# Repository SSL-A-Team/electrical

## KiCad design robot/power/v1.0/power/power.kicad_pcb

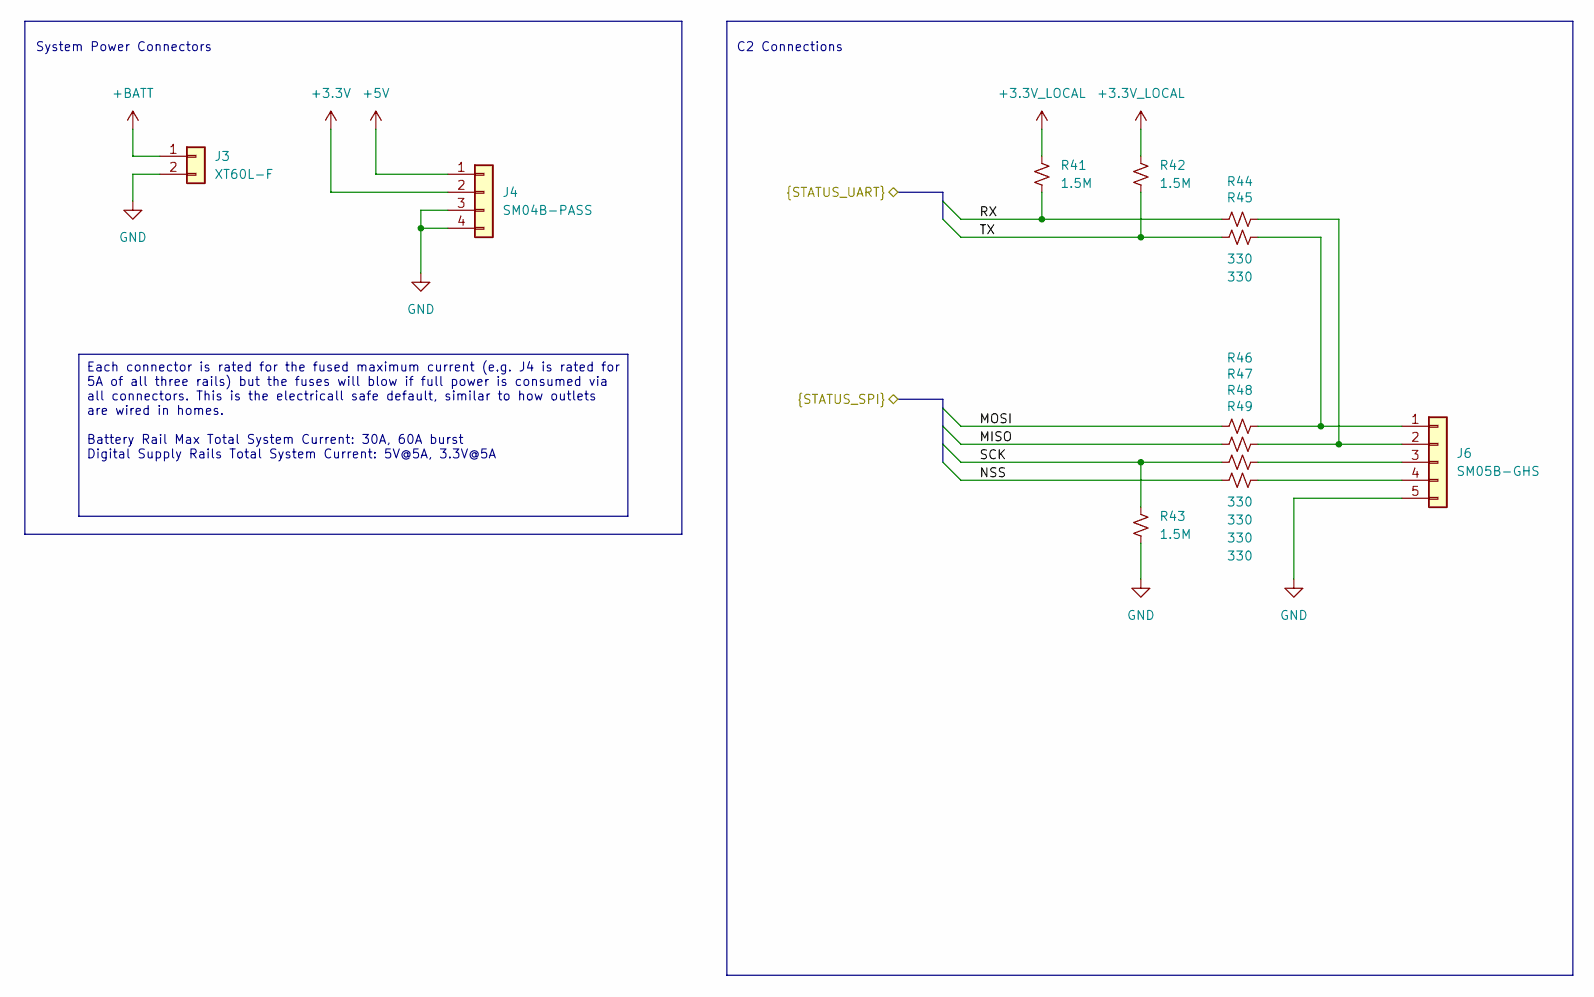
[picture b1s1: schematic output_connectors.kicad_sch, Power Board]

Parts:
J3: XT60L-F; AMASS_XT60PW-F_1x02_P7.20mm_Horizontal
J4: SM04B-PASS; JST_PA_S04B-PASS_1x04_P2.00mm_Horizontal
J6: SM05B-GHS; JST_GH_SM05B-GHS-TB_1x05-1MP_P1.25mm_Horizontal
R41, R42, R43: 1.5M; R_0402_1005Metric
R44, R45, R46, R47, R48, R49: 330; R_0402_1005Metric

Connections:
+3.3V: J4.2; also elsewhere on the board
+3.3V_LOCAL: R41.1, R42.1; also elsewhere on the board
+5V: J4.1; also elsewhere on the board
+BATT: J3.1; also elsewhere on the board
/mcu/MISO: R47.1; also elsewhere on the board
/mcu/MOSI: R46.1; also elsewhere on the board
/mcu/NSS: R49.1; also elsewhere on the board
/mcu/RX: R41.2, R44.1; also elsewhere on the board
/mcu/SCK: R43.1, R48.1; also elsewhere on the board
/mcu/TX: R42.2, R45.1; also elsewhere on the board
GND: J3.2, J4.3, J4.4, J6.5, R43.2; also elsewhere on the board
unnamed: J6.1, R45.2, R46.2
unnamed: J6.2, R44.2, R47.2
unnamed: J6.3, R48.2
unnamed: J6.4, R49.2

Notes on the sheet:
Each connector is rated for the fused maximum current (e.g. J4 is rated for 5A of all three rails) but the fuses will blow if full power is consumed via all connectors. This is the electricall safe default, similar to how outlets are wired in homes. Battery Rail Max Total System Current: 30A, 60A b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
C2 Connections
System Power Connectors

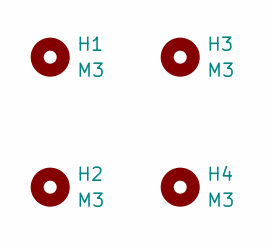
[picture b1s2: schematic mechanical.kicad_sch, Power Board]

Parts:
H1, H2, H3, H4: M3; MountingHole_3.2mm_M3_Pad_TopBottom

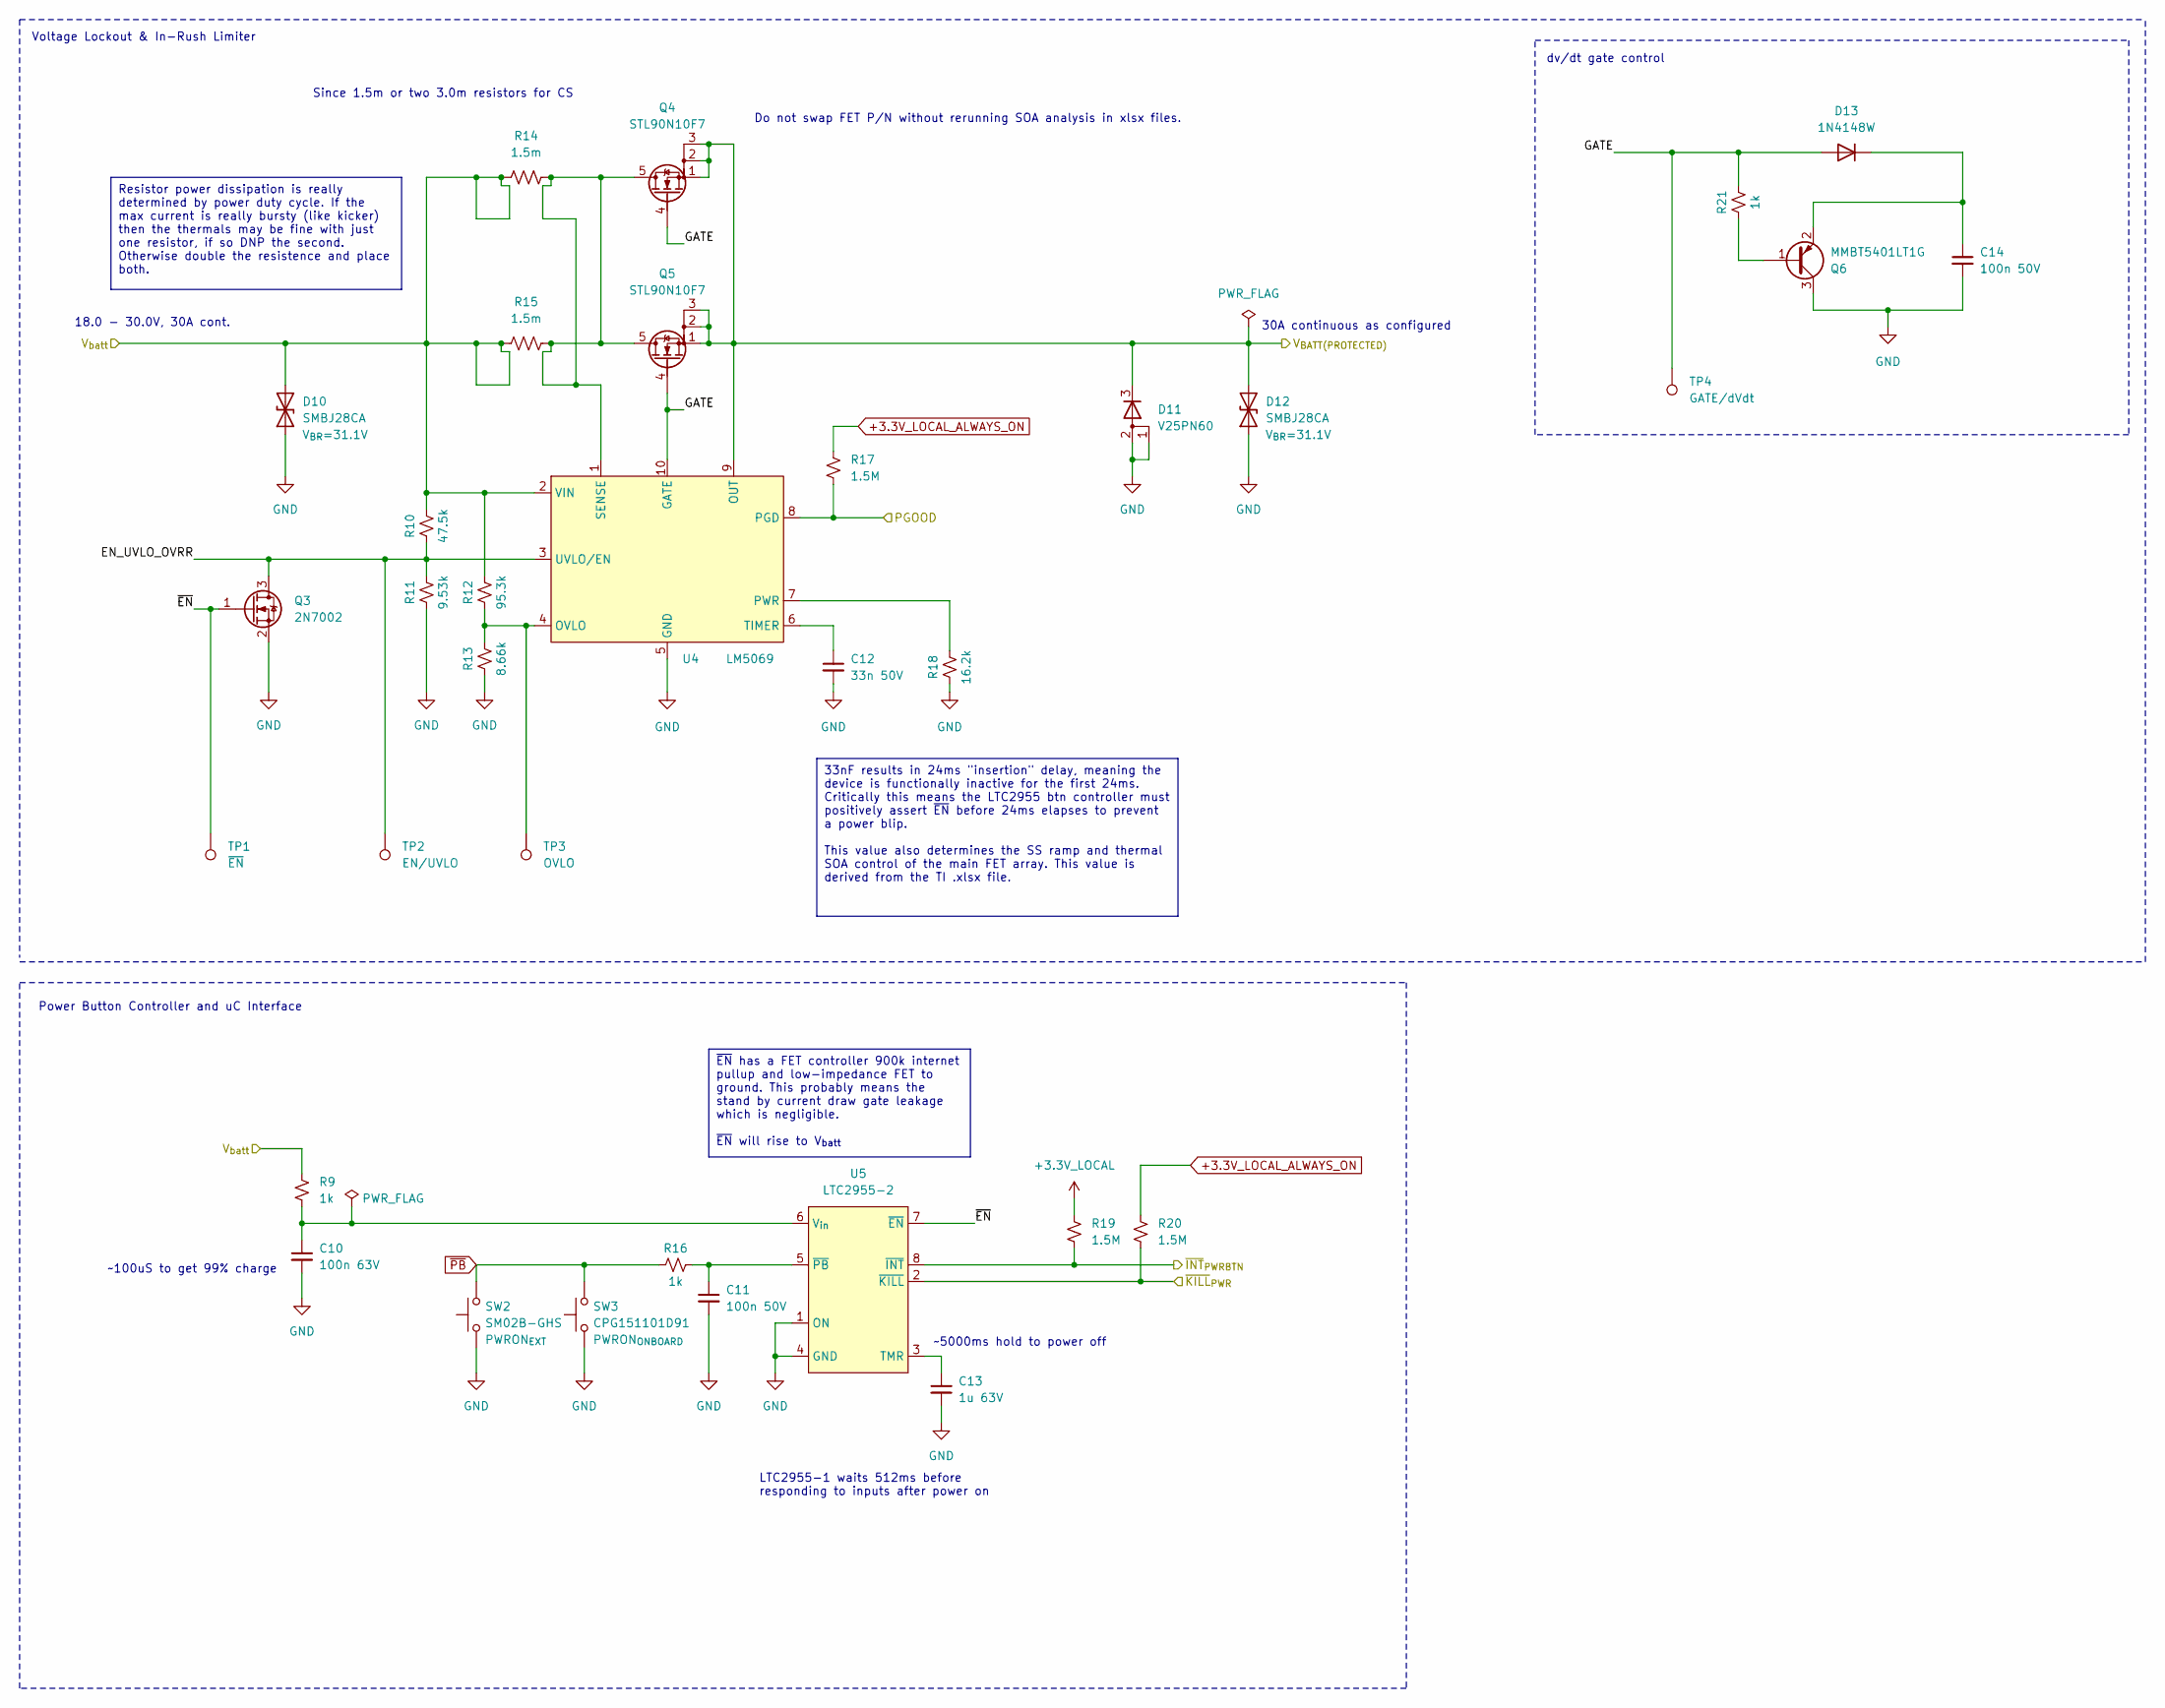
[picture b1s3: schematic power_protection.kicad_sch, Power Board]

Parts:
C10: 100n 63V; C_0402_1005Metric
C11, C14: 100n 50V; C_0402_1005Metric
C12: 33n 50V; C_0402_1005Metric
C13: 1u 63V; C_1206_3216Metric
D10, D12: SMBJ28CA; D_SMB_Non-Polar
D11: V25PN60; TO-277A
D13: 1N4148W; D_SOD-123
Q3: 2N7002; SOT-23
Q4, Q5: STL90N10F7; PowerFLAT_5x6
Q6: MMBT5401LT1G; SOT-23
R9, R16, R21: 1k; R_0402_1005Metric
R10: 47.5k; R_0402_1005Metric
R11: 9.53k; R_0402_1005Metric
R12: 95.3k; R_0402_1005Metric
R13: 8.66k; R_0402_1005Metric
R14, R15: 1.5m; R_2512_6332Metric
R17, R19, R20: 1.5M; R_0402_1005Metric
R18: 16.2k; R_0402_1005Metric
SW2: SM02B-GHS; JST_GH_SM02B-GHS-TB_1x02-1MP_P1.25mm_Horizontal
SW3: CPG151101D91; SW_SPST_TL3305A
TP1: ~{EN}; TestPoint_Pad_D2.5mm
TP2: EN/UVLO; TestPoint_Pad_D2.5mm
TP3: OVLO; TestPoint_Pad_D2.5mm
TP4: GATE/dVdt; TestPoint_Pad_D2.5mm
U4: LM5069; VSSOP-10_3x3mm_P0.5mm
U5: LTC2955-2; TSOT-23-8_HandSoldering

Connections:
+3.3V_LOCAL: R19.1; also elsewhere on the board
+3.3V_LOCAL_ALWAYS_ON: R17.1, R20.1; also elsewhere on the board
+BATT: D11.3 (K), D12.2 (A2), Q4.1 (S), Q4.2 (S), Q4.3 (S), Q5.1 (S), Q5.2 (S), Q5.3 (S), U4.9 (OUT); also elsewhere on the board
+V_{batt_fused}: D10.2 (A2), R9.2, R10.1, R12.1, R14.1, R15.1, U4.2 (VIN); also elsewhere on the board
/mcu/LOAD_SW_PGOOD: R17.2, U4.8 (PGD); also elsewhere on the board
/mcu/PWR_BTN_~INT: R19.2, U5.8 (~INT); also elsewhere on the board
/mcu/PWR_~KILL: R20.2, U5.2 (~KILL); also elsewhere on the board
/power_protection/EN_UVLO_OVRR: Q3.3 (D), R10.2, R11.1, TP2.1, U4.3 (UVLO/EN)
/power_protection/GATE: D13.2 (A), Q4.4 (G), Q5.4 (G), R21.1, TP4.1, U4.10 (GATE)
/power_protection/~EN: Q3.1 (G), TP1.1, U5.7 (~EN)
GND: C10.2, C11.2, C12.2, C13.2, C14.2, D10.1 (A1), D11.1 (A), D11.2 (A), D12.1 (A1), Q3.2 (S), Q6.3 (C), R11.2, R13.2, R18.2, SW2.1, SW3.1, U4.5 (GND), U5.1 (ON), U5.4 (GND); also elsewhere on the board
unnamed: C14.1, D13.1 (K), Q6.2 (E)
unnamed: Q4.5 (D), Q5.5 (D), R14.2, R15.2, U4.1 (SENSE)
unnamed: Q6.1 (B), R21.2
unnamed: R12.2, R13.1, TP3.1, U4.4 (OVLO)
unnamed: R18.1, U4.7 (PWR)
unnamed: C12.1, U4.6 (TIMER)
unnamed: C13.1, U5.3 (TMR)
unnamed: C10.1, R9.1, U5.6 (V_{in})
unnamed: C11.1, R16.1, U5.5 (~PB)
~PB: R16.2, SW2.2, SW3.2; also elsewhere on the board

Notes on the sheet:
~{EN} has a FET controller 900k internet pullup and low-impedance FET to ground. This probably means the stand by current draw gate leakage which is negligible. ~{EN} will rise to V_{batt}
Resistor power dissipation is really determined by power duty cycle. If the max current is really bursty (like kicker) then the thermals may be fine with just one resistor, if so DNP the second. Otherwise double the resistence and place both.
33nF results in 24ms "insertion" delay, meaning the device is functionally inactive for the first 24ms. Critically this means the LTC2955 btn controller must positively assert ~{EN} before 24ms elapses to prevent a power blip. This value also determines the SS ramp and thermal SOA control of the ma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
18.0 - 30.0V, 30A cont.
30A continuous as configured
Voltage Lockout & In-Rush Limiter
Since 1.5m or two 3.0m resistors for CS
~5000ms hold to power off
dv/dt gate control
LTC2955-1 waits 512ms before responding to inputs after power on
Power Button Controller and uC Interface
Do not swap FET P/N without rerunning SOA analysis in xlsx files.
~100uS to get 99% charge

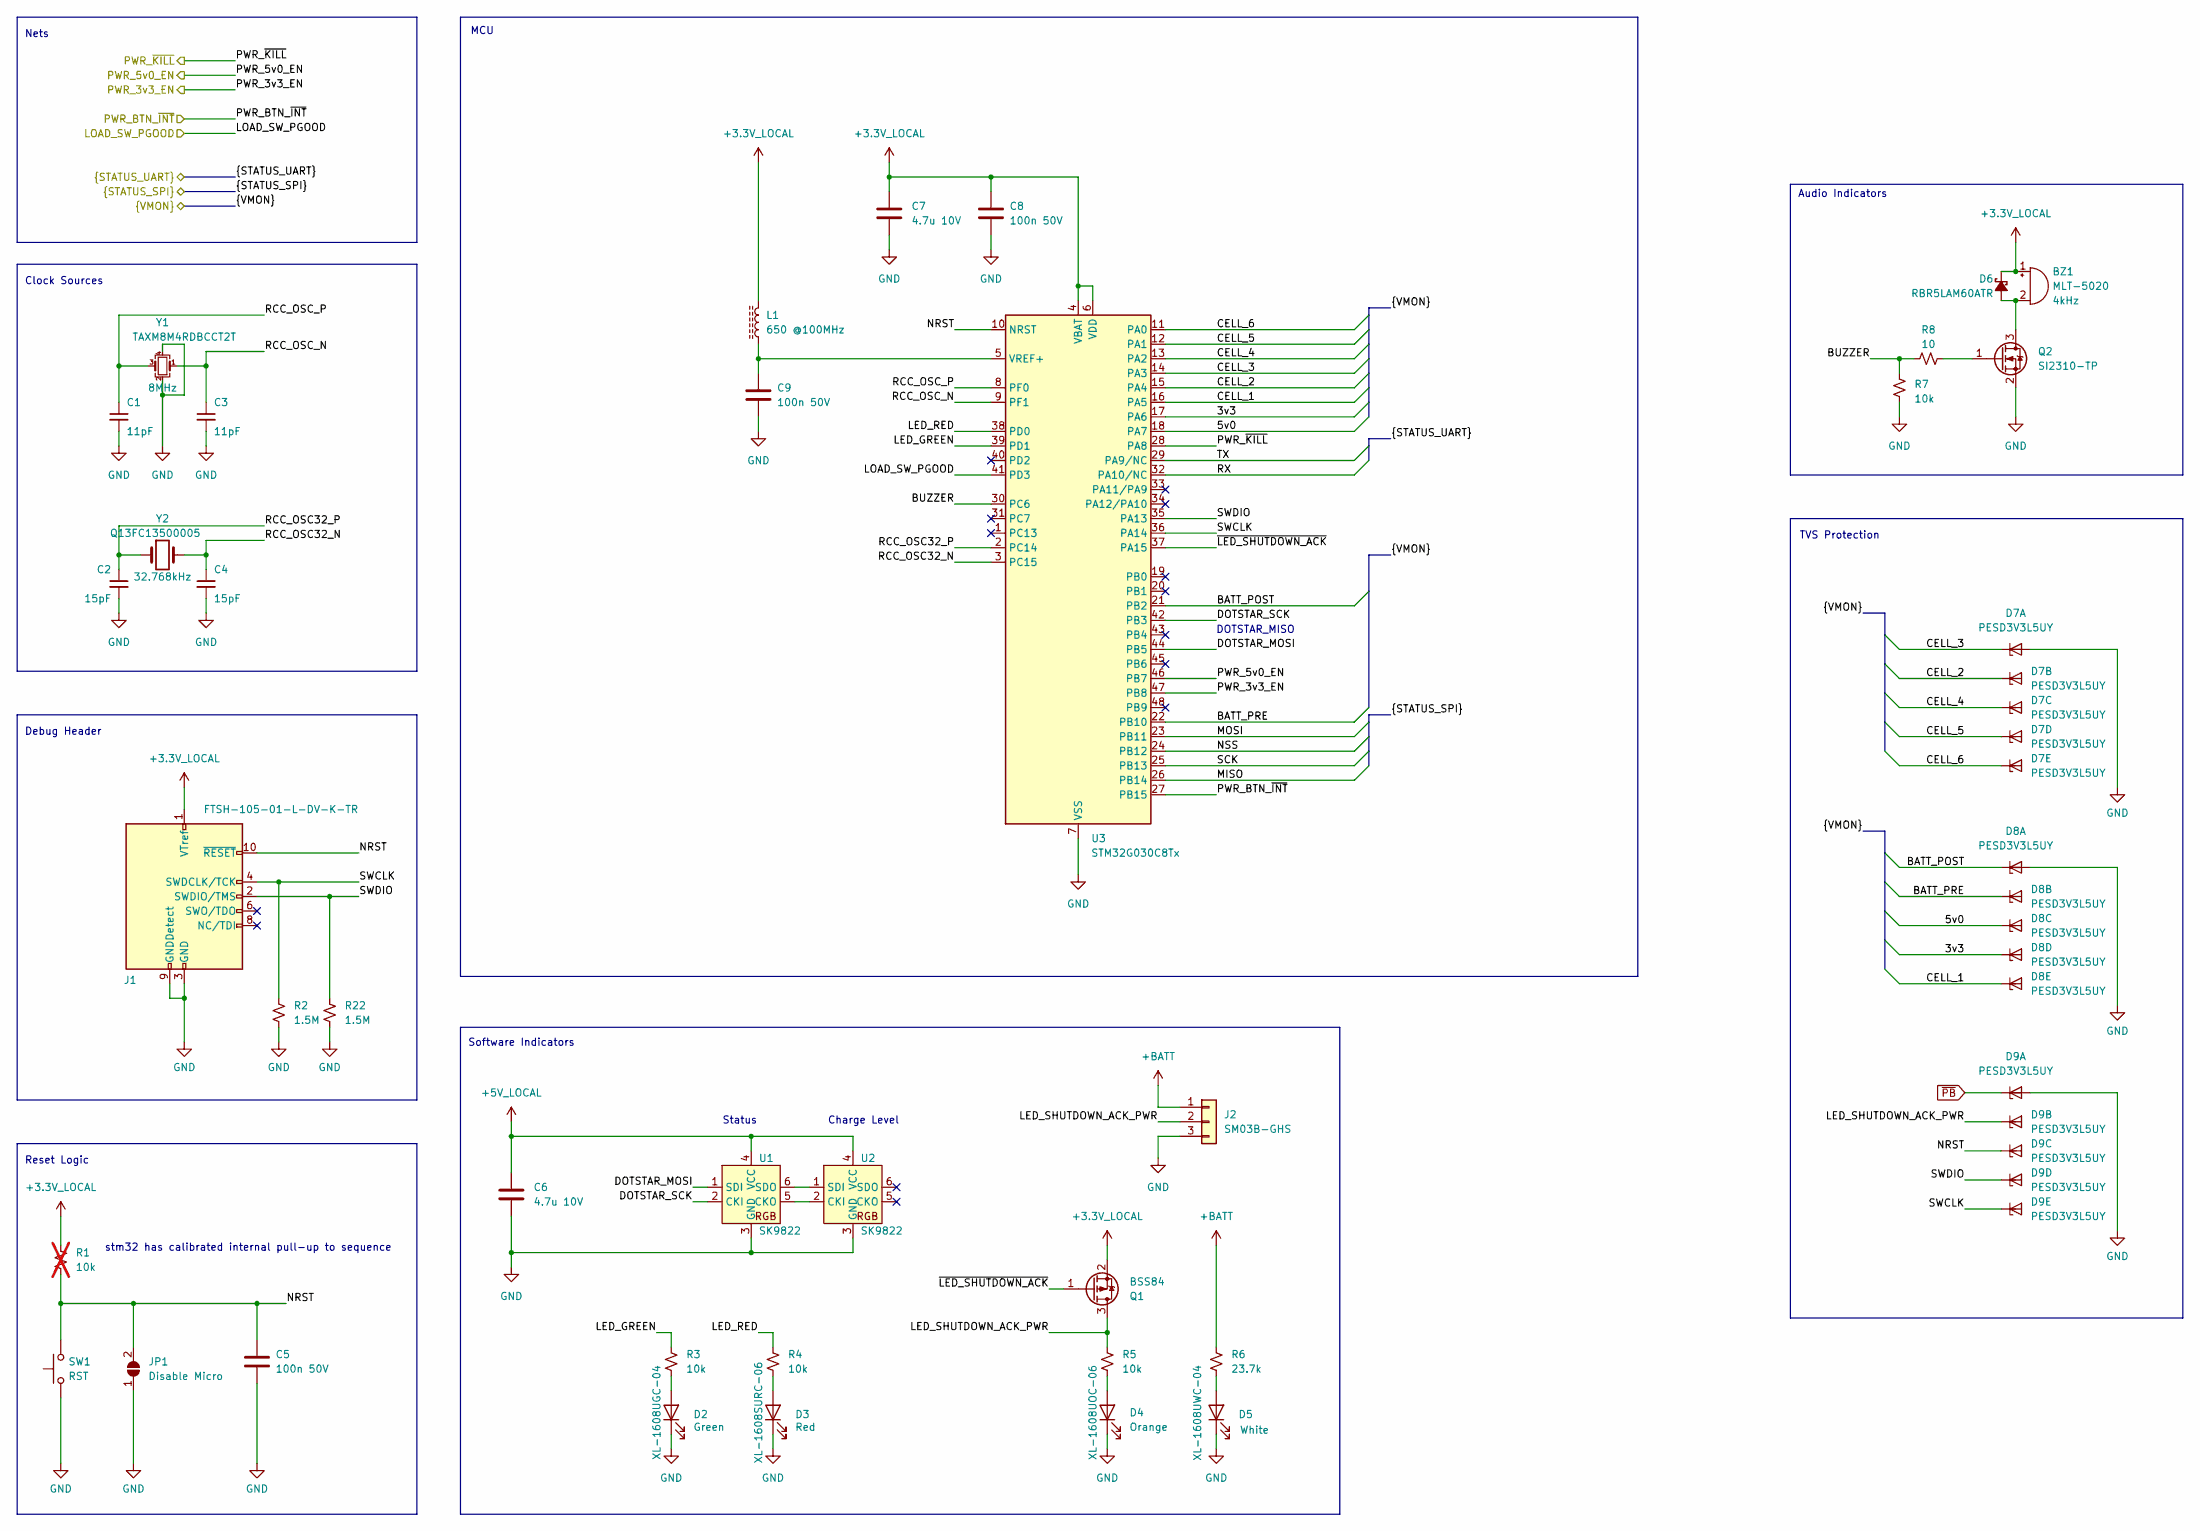
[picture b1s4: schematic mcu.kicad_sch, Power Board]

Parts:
BZ1: MLT-5020
C1, C3: 11pF; C_0402_1005Metric
C2, C4: 15pF; C_0402_1005Metric
C5, C8, C9: 100n 50V; C_0402_1005Metric
C6, C7: 4.7u 10V; C_0402_1005Metric
D2: XL-1608UGC-04; LED0603
D3: XL-1608SURC-06; LED0603
D4: XL-1608UOC-06; LED0603
D5: XL-1608UWC-04; LED0603
D6: RBR5LAM60ATR; D_SOD-128
D7, D8, D9: PESD3V3L5UY; SOT-363_SC-70-6
J1: FTSH-105-01-L-DV-K-TR; Samtec-2x5pin-0.5mm
J2: SM03B-GHS; JST_GH_SM03B-GHS-TB_1x03-1MP_P1.25mm_Horizontal
JP1: Disable Micro; SolderJumper-2_2.0x1.2mm_Open
L1: 650 @100MHz; R_0603_1608Metric
Q1: BSS84; SOT-23
Q2: SI2310-TP; SOT-23
R1: 10k; R_0402_1005Metric; not fitted
R2, R22: 1.5M; R_0402_1005Metric
R3, R4, R5, R7: 10k; R_0402_1005Metric
R6: 23.7k; R_0402_1005Metric
R8: 10; R_0402_1005Metric
SW1: RST; SW_SPST_TL3305A
U1, U2: SK9822
U3: STM32G030C8Tx; LQFP-48_7x7mm_P0.5mm
Y1: TAXM8M4RDBCCT2T; Crystal_SMD_3225-4Pin_3.2x2.5mm
Y2: Q13FC13500005; Crystal_SMD_3215-2Pin_3.2x1.5mm

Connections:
+3.3V_LOCAL: BZ1.1 (-), C7.1, C8.1, D6.1 (K), J1.1 (VTref), L1.2, Q1.2 (S), R1.1, U3.4 (VBAT), U3.6 (VDD); also elsewhere on the board
+5V_LOCAL: C6.2, U1.4 (VCC), U2.4 (VCC); also elsewhere on the board
+BATT: J2.1, R6.1; also elsewhere on the board
/mcu/3v3: D8.5 (K4), U3.17 (PA6); also elsewhere on the board
/mcu/5v0: D8.4 (K3), U3.18 (PA7); also elsewhere on the board
/mcu/BATT_POST: D8.1 (K1), U3.21 (PB2); also elsewhere on the board
/mcu/BATT_PRE: D8.3 (K2), U3.22 (PB10); also elsewhere on the board
/mcu/BUZZER: R7.1, R8.1, U3.30 (PC6)
/mcu/CELL_1: D8.6 (K5), U3.16 (PA5); also elsewhere on the board
/mcu/CELL_2: D7.3 (K2), U3.15 (PA4); also elsewhere on the board
/mcu/CELL_3: D7.1 (K1), U3.14 (PA3); also elsewhere on the board
/mcu/CELL_4: D7.4 (K3), U3.13 (PA2); also elsewhere on the board
/mcu/CELL_5: D7.5 (K4), U3.12 (PA1); also elsewhere on the board
/mcu/CELL_6: D7.6 (K5), U3.11 (PA0); also elsewhere on the board
/mcu/DOTSTAR_MOSI: U1.1 (SDI), U3.44 (PB5)
/mcu/DOTSTAR_SCK: U1.2 (CKI), U3.42 (PB3)
/mcu/LED_GREEN: R3.1, U3.39 (PD1)
/mcu/LED_RED: R4.1, U3.38 (PD0)
/mcu/LED_SHUTDOWN_ACK_PWR: D9.3 (K2), J2.2, Q1.3 (D), R5.1
/mcu/LOAD_SW_PGOOD: U3.41 (PD3); also elsewhere on the board
/mcu/MISO: U3.26 (PB14); also elsewhere on the board
/mcu/MOSI: U3.23 (PB11); also elsewhere on the board
/mcu/NRST: C5.1, D9.4 (K3), J1.10 (~RESET), JP1.2 (B), R1.2, SW1.2, U3.10 (NRST)
/mcu/NSS: U3.24 (PB12); also elsewhere on the board
/mcu/PWR_3v3_EN: U3.47 (PB8); also elsewhere on the board
/mcu/PWR_5v0_EN: U3.46 (PB7); also elsewhere on the board
/mcu/PWR_BTN_~INT: U3.27 (PB15); also elsewhere on the board
/mcu/PWR_~KILL: U3.28 (PA8); also elsewhere on the board
/mcu/RCC_OSC32_N: C4.1, U3.3 (PC15), Y2.2
/mcu/RCC_OSC32_P: C2.1, U3.2 (PC14), Y2.1
/mcu/RCC_OSC_N: C3.1, U3.9 (PF1), Y1.1
/mcu/RCC_OSC_P: C1.1, U3.8 (PF0), Y1.3
/mcu/RX: U3.32 (PA10/NC); also elsewhere on the board
/mcu/SCK: U3.25 (PB13); also elsewhere on the board
/mcu/SWCLK: D9.6 (K5), J1.4 (SWDCLK/TCK), R2.1, U3.36 (PA14)
/mcu/SWDIO: D9.5 (K4), J1.2 (SWDIO/TMS), R22.1, U3.35 (PA13)
/mcu/TX: U3.29 (PA9/NC); also elsewhere on the board
/mcu/~LED_SHUTDOWN_ACK: Q1.1 (G), U3.37 (PA15)
GND: C1.2, C2.2, C3.2, C4.2, C5.2, C6.1, C7.2, C8.2, C9.2, D2.1 (K), D3.1 (K), D4.1 (K), D5.1 (K), D7.2 (A), D8.2 (A), D9.2 (A), J1.3 (GND), J1.5 (GND), J1.9 (GNDDetect), J2.3, JP1.1 (A), Q2.2 (S), R2.2, R7.2, R22.2, SW1.1, U1.3 (GND), U2.3 (GND), U3.7 (VSS), Y1.2, Y1.4; also elsewhere on the board
unnamed: BZ1.2 (+), D6.2 (A), Q2.3 (D)
unnamed: D2.2 (A), R3.2
unnamed: D3.2 (A), R4.2
unnamed: D4.2 (A), R5.2
unnamed: D5.2 (A), R6.2
unnamed: Q2.1 (G), R8.2
unnamed: U1.5 (CKO), U2.2 (CKI)
unnamed: U1.6 (SDO), U2.1 (SDI)
unnamed: C9.1, L1.1, U3.5 (VREF+)
~PB: D9.1 (K1); also elsewhere on the board

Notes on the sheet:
Charge Level
Nets
Reset Logic
Audio Indicators
stm32 has calibrated internal pull-up to sequence
Clock Sources
TVS Protection
Status
Software Indicators
MCU
Debug Header
DOTSTAR_MISO

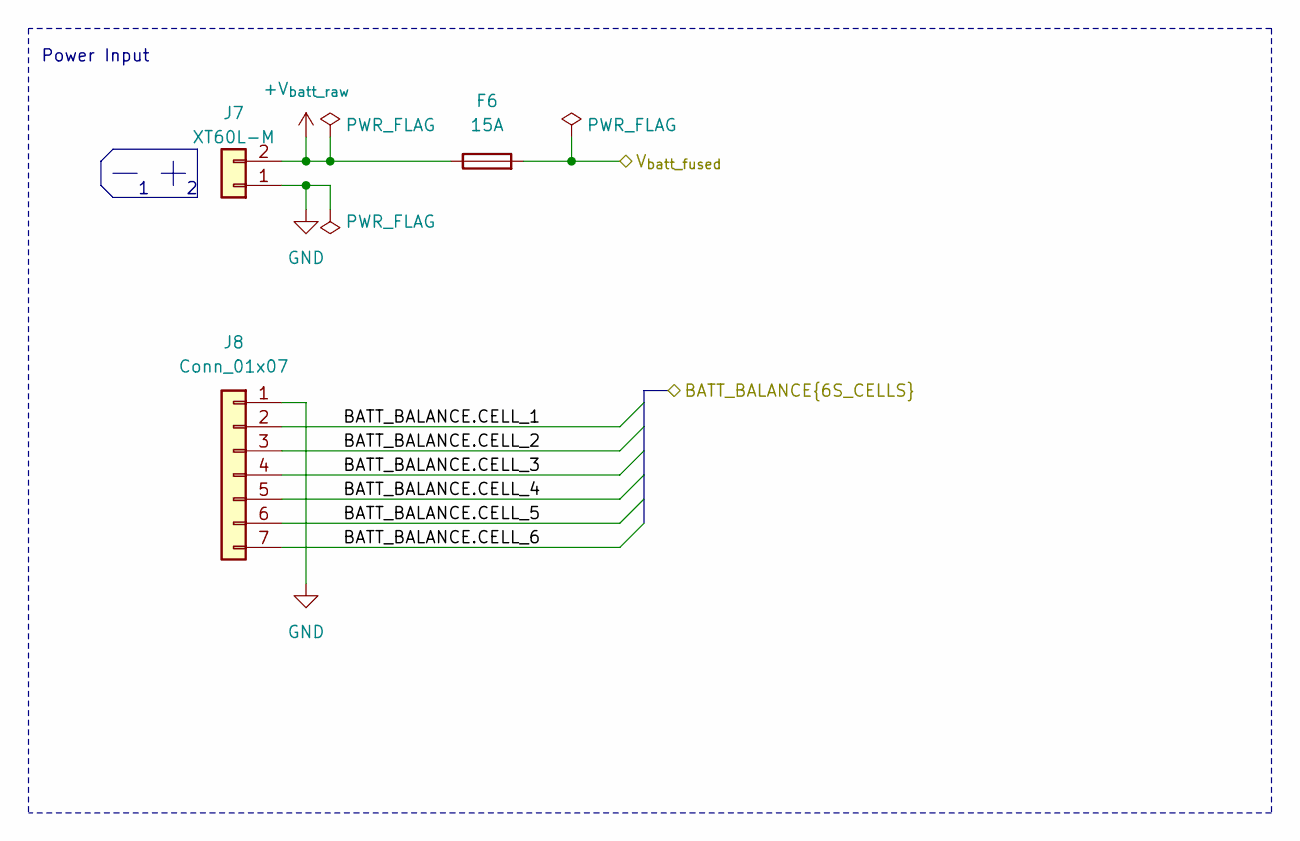
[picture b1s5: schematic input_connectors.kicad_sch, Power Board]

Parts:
F6: 15A; 3557-2
J7: XT60L-M; AMASS_XT60PW-M_1x02_P7.20mm_Horizontal
J8: Conn_01x07; JST_XH_S7B-XH-A_1x07_P2.50mm_Horizontal; LCSC C157916

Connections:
+V_{batt_fused}: F6.2; also elsewhere on the board
+V_{batt_raw}: F6.1, J7.2
/input_connectors/BATT_BALANCE.CELL_1: J8.2; also elsewhere on the board
/input_connectors/BATT_BALANCE.CELL_2: J8.3; also elsewhere on the board
/input_connectors/BATT_BALANCE.CELL_3: J8.4; also elsewhere on the board
/input_connectors/BATT_BALANCE.CELL_4: J8.5; also elsewhere on the board
/input_connectors/BATT_BALANCE.CELL_5: J8.6; also elsewhere on the board
/input_connectors/BATT_BALANCE.CELL_6: J8.7; also elsewhere on the board
GND: J7.1, J8.1; also elsewhere on the board

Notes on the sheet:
Power Input

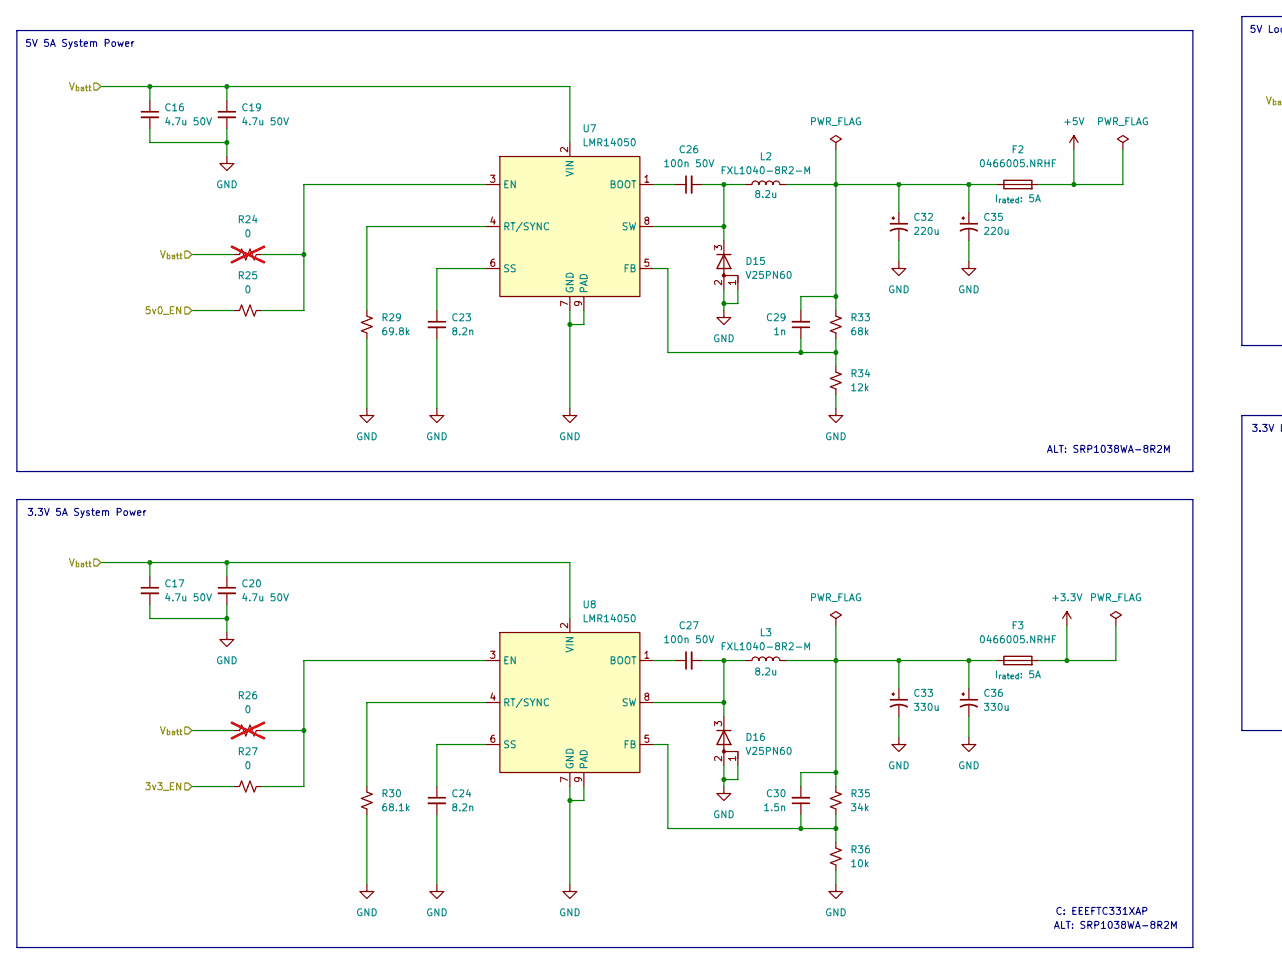
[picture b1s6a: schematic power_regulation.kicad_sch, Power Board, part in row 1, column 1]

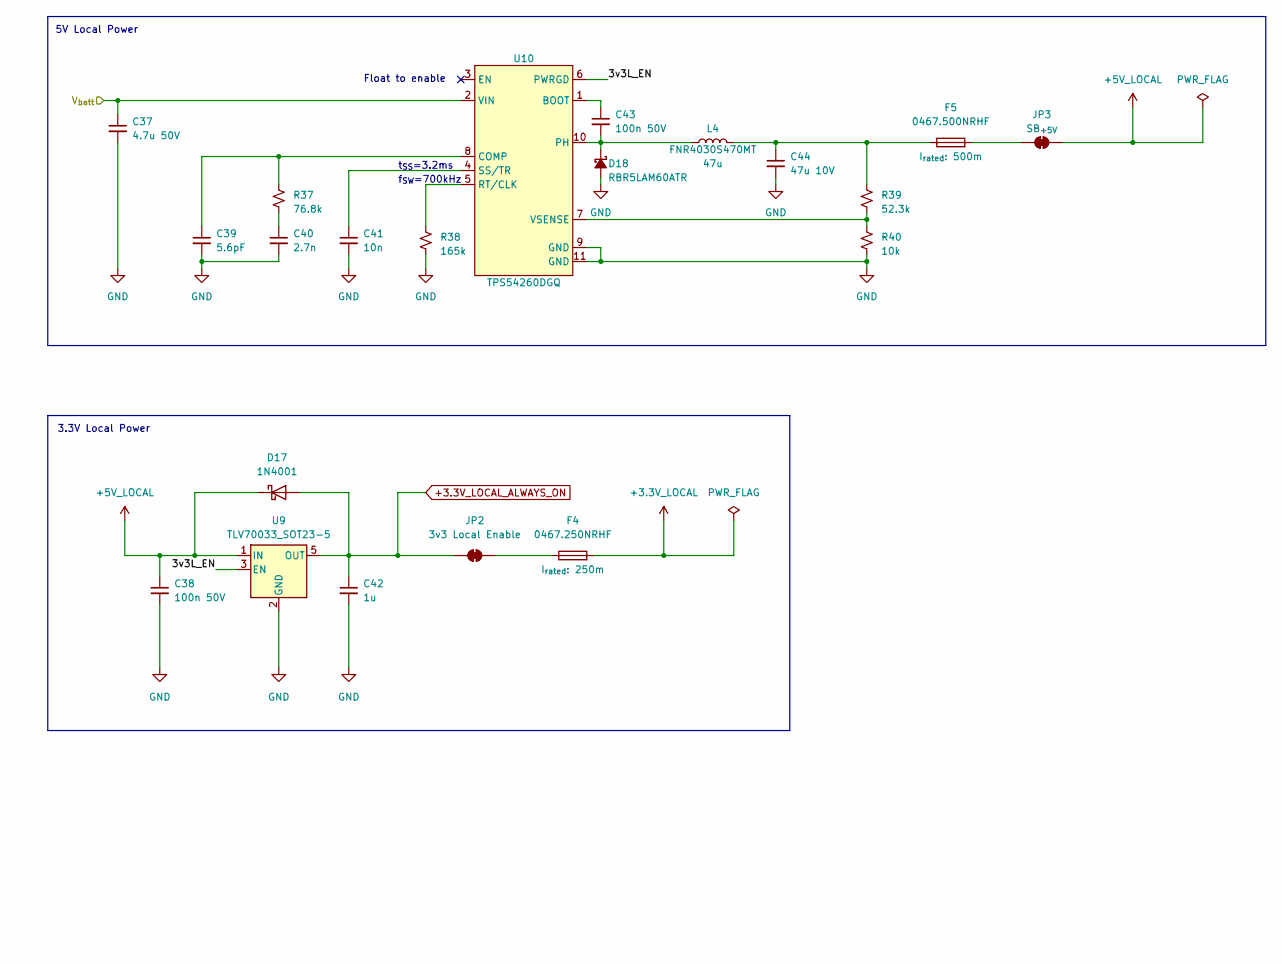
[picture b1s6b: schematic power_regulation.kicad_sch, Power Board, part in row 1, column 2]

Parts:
C16, C17, C19, C20, C37: 4.7u 50V; C_0805_2012Metric
C23, C24: 8.2n; C_0402_1005Metric
C26, C27, C38, C43: 100n 50V; C_0402_1005Metric
C29: 1n; C_0402_1005Metric
C30: 1.5n; C_0402_1005Metric
C32, C35: 220u; CP_Elec_6.3x5.8
C33, C36: 330u; CP_Elec_6.3x7.7
C39: 5.6pF; C_0402_1005Metric
C40: 2.7n; C_0402_1005Metric
C41: 10n; C_0402_1005Metric
C42: 1u; C_1206_3216Metric
C44: 47u 10V; C_1210_3225Metric
D15, D16: V25PN60; TO-277A
D17: 1N4001; D_SMA
D18: RBR5LAM60ATR; D_SOD-128
F2, F3: 0466005.NRHF; Fuse_1206_3216Metric_Pad1.42x1.75mm_HandSolder
F4: 0467.250NRHF; Fuse_0603_1608Metric_Pad1.05x0.95mm_HandSolder
F5: 0467.500NRHF; Fuse_0603_1608Metric_Pad1.05x0.95mm_HandSolder
JP2: 3v3 Local Enable; SolderJumper-2_2.0x1.2mm_Closed
JP3: SB_{+5V}; SolderJumper-2_2.0x1.2mm_Closed
L2, L3: FXL1040-8R2-M; L_Bourns_SRP1038C_10.0x10.0mm
L4: FNR4030S470MT; L_Changjiang_FNR4030S
R24, R26: 0; R_0402_1005Metric; not fitted
R25, R27: 0; R_0402_1005Metric
R29: 69.8k; R_0402_1005Metric
R30: 68.1k; R_0402_1005Metric
R33: 68k; R_0402_1005Metric
R34: 12k; R_0402_1005Metric
R35: 34k; R_0402_1005Metric
R36, R40: 10k; R_0402_1005Metric
R37: 76.8k; R_0402_1005Metric
R38: 165k; R_0402_1005Metric
R39: 52.3k; R_0402_1005Metric
U7, U8: LMR14050; SOIC-8-1EP_3.9x4.9mm_P1.27mm_EP2.29x3mm
U9: TLV70033_SOT23-5; SOT-23-5
U10: TPS54260DGQ; HVSSOP-10-1EP_3x3mm_P0.5mm_EP1.57x1.88mm

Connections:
+3.3V: F3.2; also elsewhere on the board
+3.3V_LOCAL: F4.2; also elsewhere on the board
+3.3V_LOCAL_ALWAYS_ON: C42.1, D17.2 (A), JP2.1 (A), U9.5 (OUT); also elsewhere on the board
+5V: F2.2; also elsewhere on the board
+5V_LOCAL: C38.1, D17.1 (K), JP3.2 (B), U9.1 (IN); also elsewhere on the board
+BATT: C16.1, C17.1, C19.1, C20.1, C37.1, R24.1, R26.1, U7.2 (VIN), U8.2 (VIN), U10.2 (VIN); also elsewhere on the board
/mcu/PWR_3v3_EN: R27.1; also elsewhere on the board
/mcu/PWR_5v0_EN: R25.1; also elsewhere on the board
/power_regulation/3v3L_EN: U9.3 (EN), U10.6 (PWRGD)
GND: C16.2, C17.2, C19.2, C20.2, C23.2, C24.2, C32.2, C33.2, C35.2, C36.2, C37.2, C38.2, C39.2, C40.2, C41.2, C42.2, C44.2, D15.1 (A), D15.2 (A), D16.1 (A), D16.2 (A), D18.2 (A), R29.1, R30.1, R34.1, R36.1, R38.2, R40.2, U7.7 (GND), U7.9 (PAD), U8.7 (GND), U8.9 (PAD), U9.2 (GND), U10.9 (GND), U10.11 (GND); also elsewhere on the board
unnamed: C29.2, C32.1, C35.1, F2.1, L2.2, R33.2
unnamed: C30.2, C33.1, C36.1, F3.1, L3.2, R35.2
unnamed: C40.1, R37.2
unnamed: C44.1, F5.1, L4.2, R39.1
unnamed: C26.2, D15.3 (K), L2.1, U7.8 (SW)
unnamed: C27.2, D16.3 (K), L3.1, U8.8 (SW)
unnamed: C43.2, D18.1 (K), L4.1, U10.10 (PH)
unnamed: F4.1, JP2.2 (B)
unnamed: F5.2, JP3.1 (A)
unnamed: C26.1, U7.1 (BOOT)
unnamed: R24.2, R25.2, U7.3 (EN)
unnamed: C29.1, R33.1, R34.2, U7.5 (FB)
unnamed: R29.2, U7.4 (RT/SYNC)
unnamed: C23.1, U7.6 (SS)
unnamed: C27.1, U8.1 (BOOT)
unnamed: R26.2, R27.2, U8.3 (EN)
unnamed: C30.1, R35.1, R36.2, U8.5 (FB)
unnamed: R30.2, U8.4 (RT/SYNC)
unnamed: C24.1, U8.6 (SS)
unnamed: C43.1, U10.1 (BOOT)
unnamed: C39.1, R37.1, U10.8 (COMP)
unnamed: R38.1, U10.5 (RT/CLK)
unnamed: C41.1, U10.4 (SS/TR)
unnamed: R39.2, R40.1, U10.7 (VSENSE)

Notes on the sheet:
ALT: SRP1038WA-8R2M
5V 5A System Power
Float to enable
C: EEEFTC331XAP
3.3V 5A System Power
f_{SW}=700kHz
3.3V Local Power
t_{SS}=3.2ms
5V Local Power
